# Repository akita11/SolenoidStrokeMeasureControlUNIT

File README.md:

# SolenoidStokeMeasureControl UNIT

ソレノイドのストローク位置によってインダクタンスが変化し、PWM制御時の電流波形が変化することを利用して、ソレノイドのPWM制御とストローク位置の計測（推定）を同時に行うための回路です。
（基板形状が「[M5Stack用VH3.96-4ピンユニット[U020]](https://www.switch-science.com/products/4055)」と同一のため、そのケースを使うことができます。）

**【注意：重要】**
実際の制御・計測の動作には、ソレノイドごとに特性の計測を行う必要があり、また特性の個体差、温度特性なども考慮する必要があります。そのため、**「これを使ってサンプルプログラムを書き込めば間違いなく動作する（制御ができる）」というものではなく、あくまでもこの原理検証の実験のための回路**ということをご理解ください。測定原理やサンプルプログラムは[こちら](https://github.com/akita11/SolenoidStrokeMeasureControl)に適宜まとめて更新していきます。

## 使い方

オレンジ色のコネクタ(VH3.96-4p)に、ソレノイド用の電源とソレノイドを接続します。M5Stackの[BAVGソケット](https://www.switch-science.com/products/7234)を使うと、電源は2.1mmプラグ、負荷はスプリング端子で接続できて便利です。

Grove端子の3番("PWM"と表記）にPWM波形を加えてソレノイドをPWM駆動し、その駆動電流が電圧波形としてGrove端子の4番（"ADC"と表記）に出力されます。

なおArduinoやM5Stack (Core2/CoreS3)用のサンプルプログラムは[こちら](https://github.com/akita11/SolenoidStrokeMeasureControl)にあります（あくまでも参考用のものです）。Measure_...がパラメータ計測用のプログラム、Control...が位置計測（推定）・位置制御用のプログラムです。（ESP32用はM5Stack Core2のPortAに本ボードを接続して使用します）

### 増幅率の調整

ソレノイドの駆動電流を0.2Ωの抵抗で電圧変換し、それをオペアンプ（非反転増幅回路）で増幅して"ADC"端子に出力しています。その増幅率は、用いるソレノイド・電源電圧からきまる駆動電流にあわせて、適切な範囲に調整する必要があります。"ADC"端子の波形をオシロ等で計測し、用いるマイコンのADCの入力電圧範囲に収まるように増幅率を調整します。増幅率は基板裏面のハンダジャンパJP3/JP4JP5で調整できます。（JP3は初期状態でONになっていますので、OFFにする場合はパターンをカットしてください）

- JP3/JP4/JP5=ON/OFF/OFF : 101倍
- JP3/JP4/JP5=ON/ON/OFF : 39倍
- JP3/JP4/JP5=ON/OFF/ON : 20倍
- JP3/JP4/JP5=ON/ON/ON : 16倍
- JP3/JP4/JP5=OFF/OFF/OFF : R1にとりつける抵抗から決まる倍率（(R1÷1[kΩ]+1)倍）

## 測定原理

ソレノイドは電気回路的にはインダクタで、そのインダクタンスはストローク（プランジャ）位置で変化します。そのためON時の充電電流の波形は、ストローク位置で変化します。ただし充電開始時の電流はOFF期間中の放電特性できまるため、ゼロからとは限りません。またPWMのON時間（PWMのデューティー比）によっても波形は変化します。

ソレノイドによっては、ON後の2箇所の時点（例えば100us後と700us後）での電流の差が、PWMのON時間（PWMのデューティー比）ごとにストローク位置に伴って変化するため、与えているPWM ON時間とその電流差から、ストローク位置を計測（推定）することができます。現時点で試した範囲では、TakahaのCBS0730シリーズはこの特性をもっています。（詳細は[arXivの論文](https://arxiv.org/abs/2405.11721)にまとめてあります）

ただしソレノイドによっては、この電流差がストロークによってほとんど変化しないため、この方法では位置を計測することができません。そのため、複数点の電流の計測値から、予め計測した位置と電流値との差（の総和）が最小となるように反復計算で位置を求めるアルゴリズムを開発中です。まだ安定性や精度の検証は不十分ですが、参考用に上記GitHubにArduinoとESP32用のソースコードをおいてあります（計測データはTakahaのLongStrokeSolenoidのもの）。

## Author

Junichi Akita (akita@ifdl.jp, @akita11)

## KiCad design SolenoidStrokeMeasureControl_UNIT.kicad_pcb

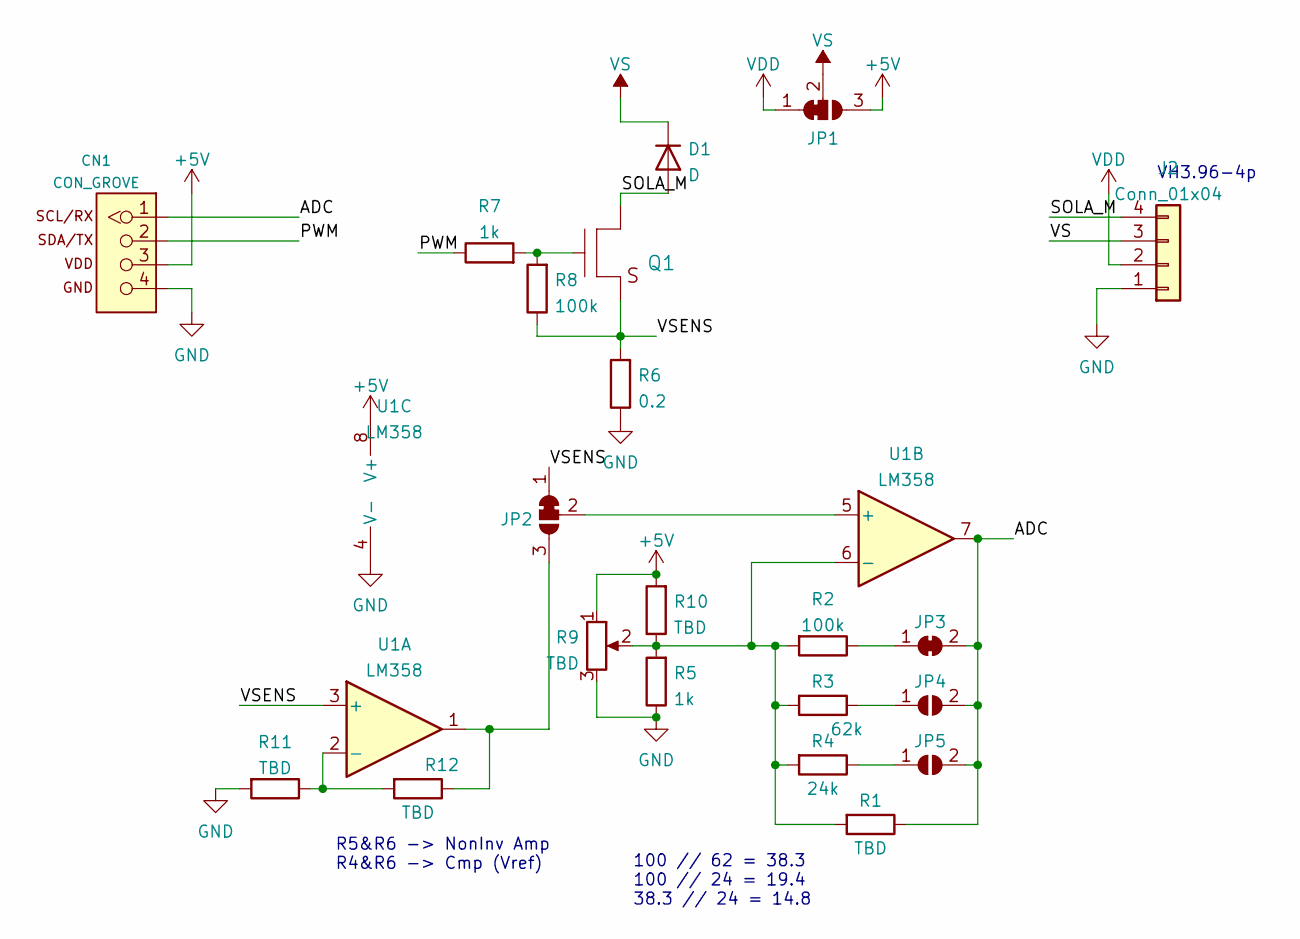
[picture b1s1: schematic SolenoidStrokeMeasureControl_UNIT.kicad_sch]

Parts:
CN1: CON_GROVE; CON_GROVE_H
D1: D; D_SOD-123F
J2: Conn_01x04; JST_VH_S4P-VH_1x04_P3.96mm_Horizontal
JP1, JP2: SolderJumper_3_Bridged12; SolderJumper-3_P1.3mm_Bridged2Bar12_Pad1.0x1.5mm
JP3: SolderJumper_2_Bridged; SolderJumper-2_P1.3mm_Bridged_Pad1.0x1.5mm
JP4, JP5: SolderJumper_2_Open; SolderJumper-2_P1.3mm_Open_Pad1.0x1.5mm
Q1: TR_NMOS_IRLML6344; SOT-23
R1: TBD; R_Axial_DIN0207_L6.3mm_D2.5mm_P2.54mm_Vertical
R2, R8: 100k; R_0603_1608Metric
R3: 62k; R_0603_1608Metric
R4: 24k; R_0603_1608Metric
R5, R7: 1k; R_0603_1608Metric
R6: 0.2; R_1206_3216Metric
R9: TBD; Potentiometer_Bourns_3223W
R10, R11, R12: TBD; R_0603_1608Metric
U1: LM358; SO-8_5.3x6.2mm_P1.27mm

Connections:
+5V: CN1.3, JP1.3 (B), R9.1, R10.2, U1.8 (V+)
/ADC: CN1.1, JP3.2 (B), JP4.2 (B), JP5.2 (B), R1.1, U1.7
/PWM: CN1.2, R7.1
/SOLA_M: D1.2 (A), J2.4, Q1.3 (D)
/VSENS: JP2.1 (A), Q1.2 (S), R6.2, R8.1, U1.3 (+)
GND: CN1.4, J2.1, R5.1, R6.1, R9.3, R11.2, U1.4 (V-)
unnamed: JP2.2 (C), U1.5 (+)
unnamed: JP2.3 (B), R12.1, U1.1
unnamed: JP4.1 (A), R3.1
unnamed: JP5.1 (A), R4.1
unnamed: Q1.1 (G), R7.2, R8.2
unnamed: JP3.1 (A), R2.1
unnamed: R1.2, R2.2, R3.2, R4.2, R5.2, R9.2, R10.1, U1.6 (-)
unnamed: R11.1, R12.2, U1.2 (-)
VDD: J2.2, JP1.1 (A)
VS: D1.1 (K), J2.3, JP1.2 (C)

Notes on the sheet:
100 // 62 = 38.3 100 // 24 = 19.4 38.3 // 24 = 14.8
R5&R6 -> NonInv Amp R4&R6 -> Cmp (Vref)
VH3.96-4p

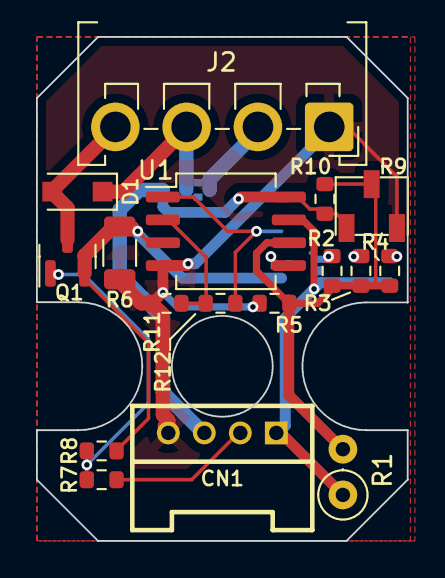
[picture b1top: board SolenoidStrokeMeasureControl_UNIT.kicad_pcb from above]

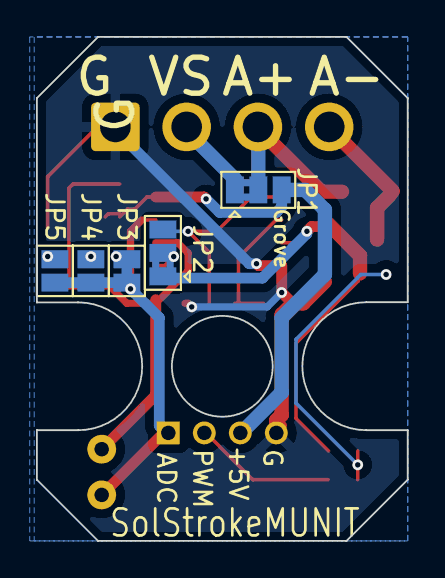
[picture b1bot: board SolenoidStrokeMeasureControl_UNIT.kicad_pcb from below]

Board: 2 copper layers, 20.6 x 28.0 mm, 22 parts (5 on the bottom side), 16 nets.

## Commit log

2024-06-15 typo fix in README
2024-06-19 add schematic, typo fix
